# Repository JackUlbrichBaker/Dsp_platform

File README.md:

### Digital Delay Pedal

This is a git repo to track changes in this digital delay pedal

Using the STM32H750 MCU, PCM3060 CODEC and the AS4C16M32MSA Memory ICs

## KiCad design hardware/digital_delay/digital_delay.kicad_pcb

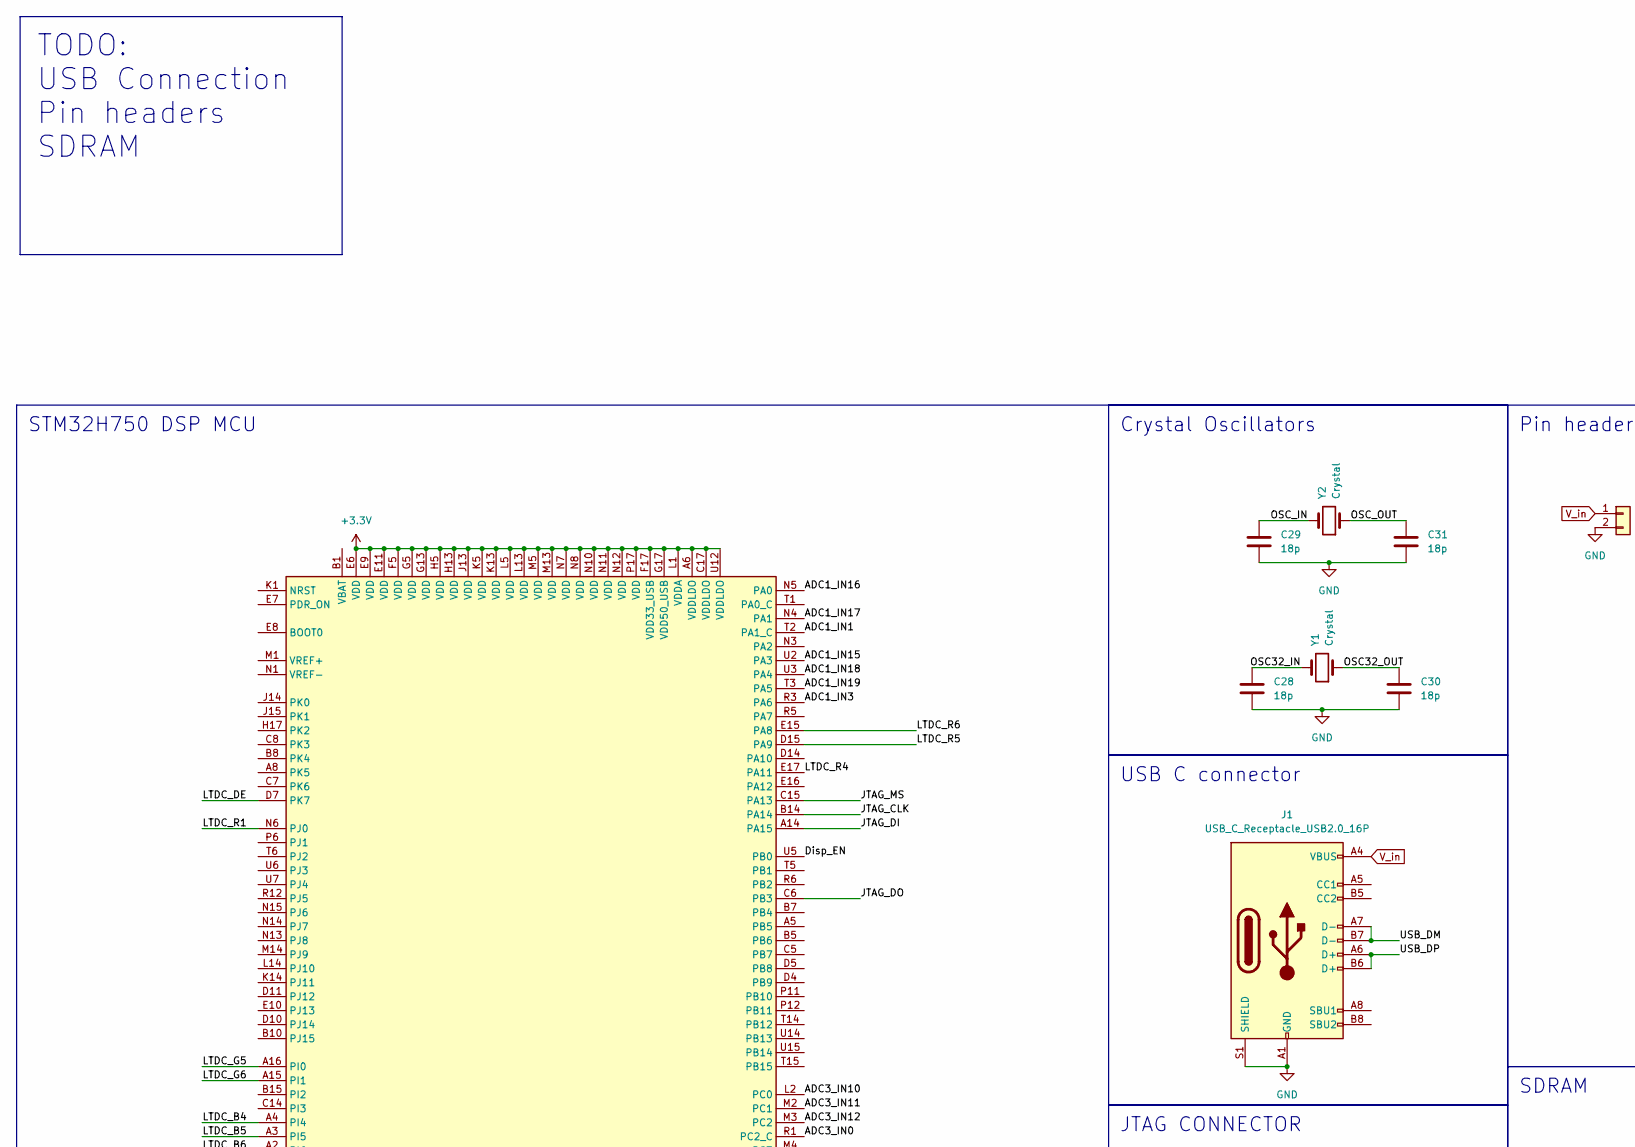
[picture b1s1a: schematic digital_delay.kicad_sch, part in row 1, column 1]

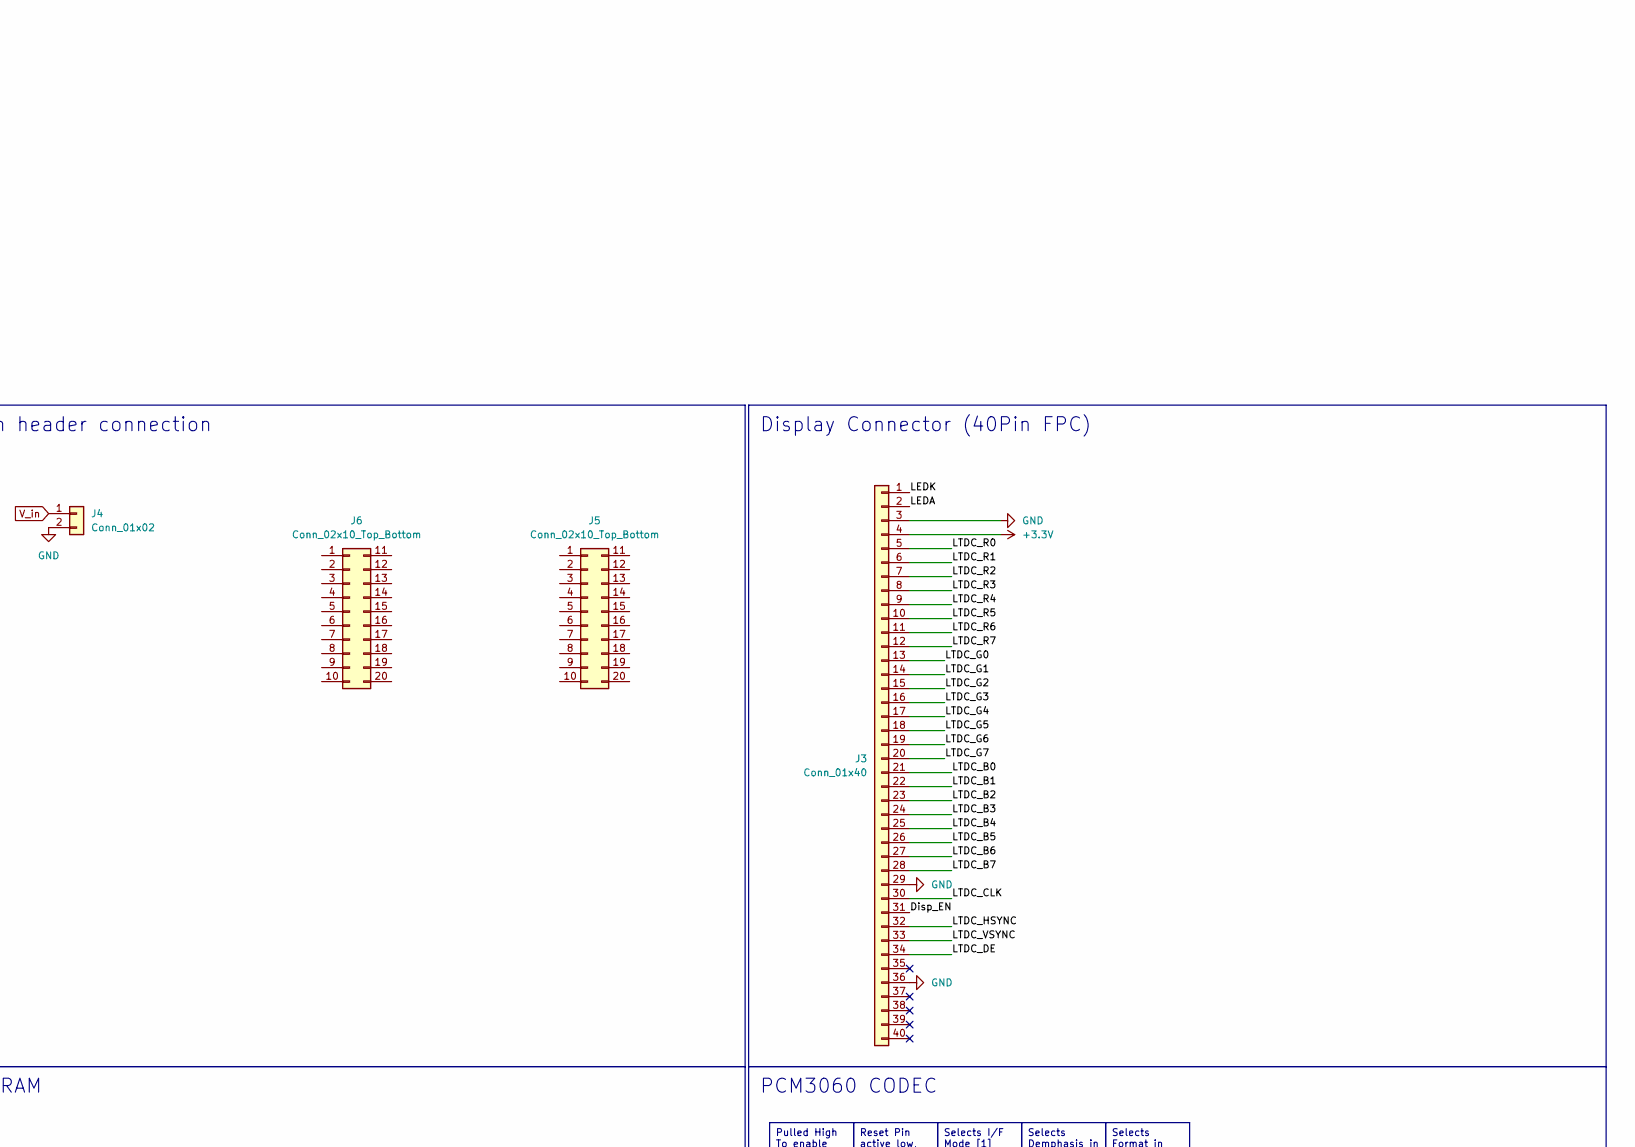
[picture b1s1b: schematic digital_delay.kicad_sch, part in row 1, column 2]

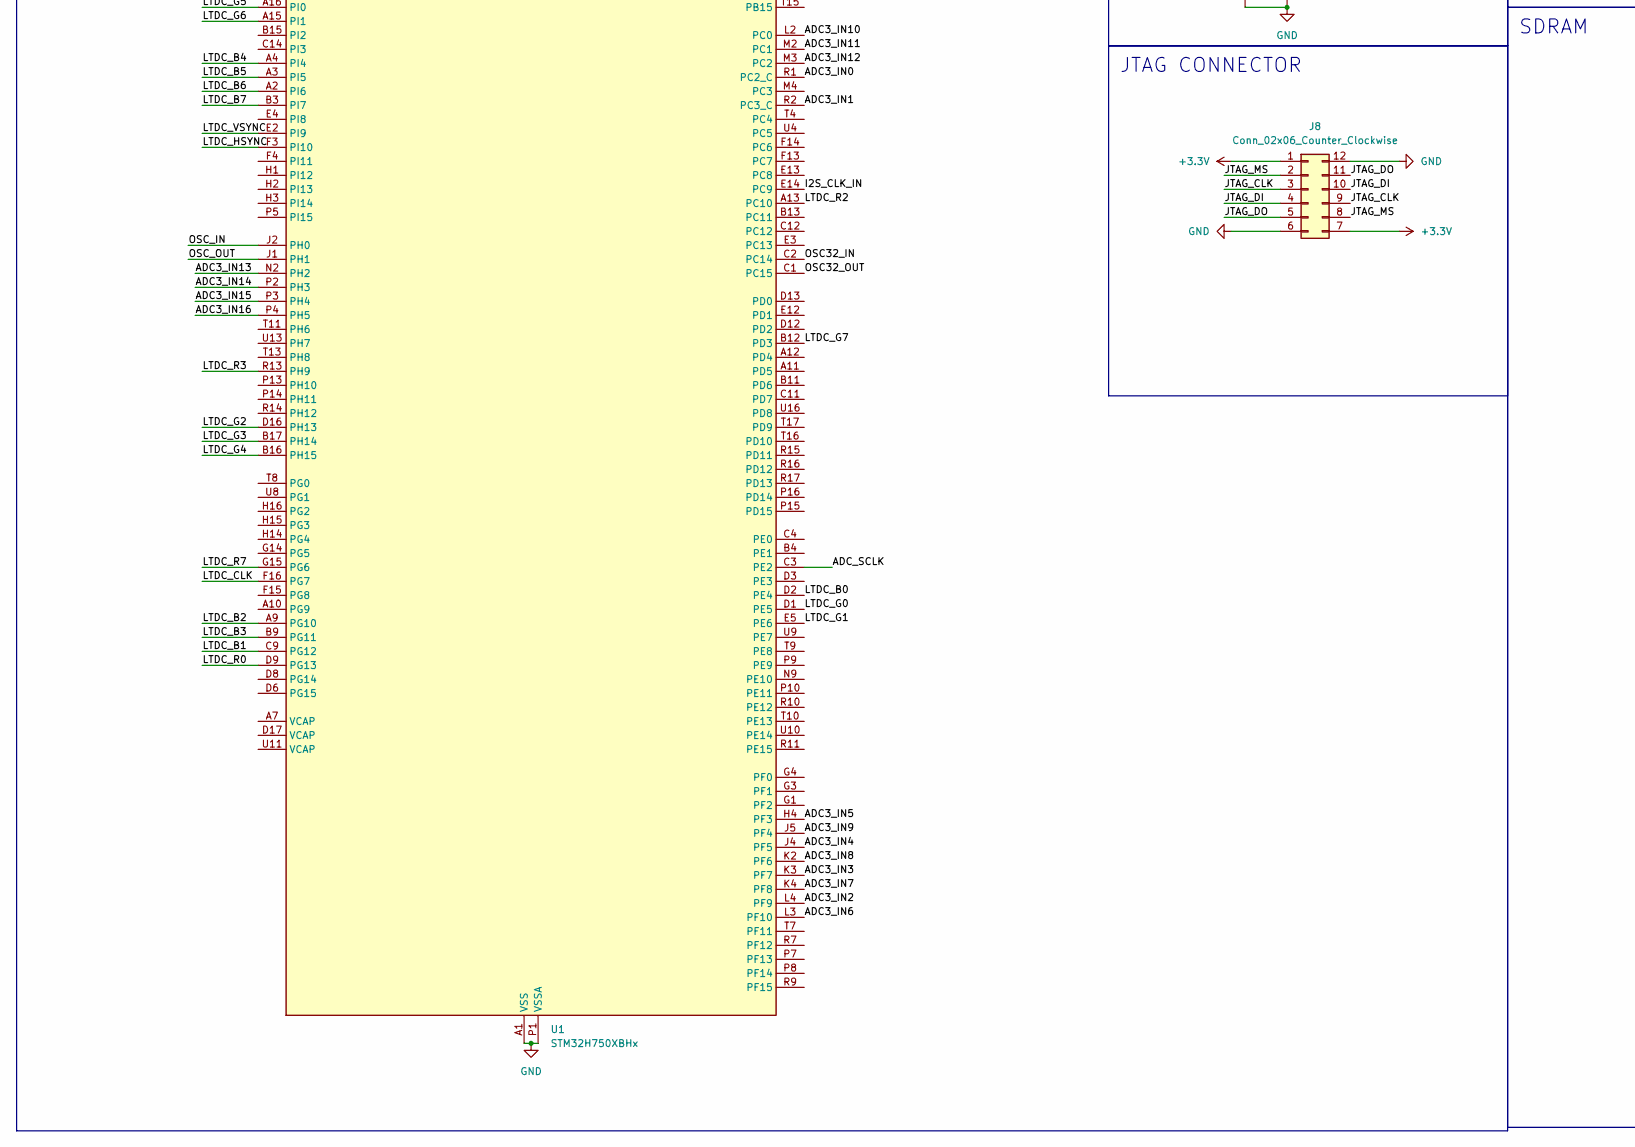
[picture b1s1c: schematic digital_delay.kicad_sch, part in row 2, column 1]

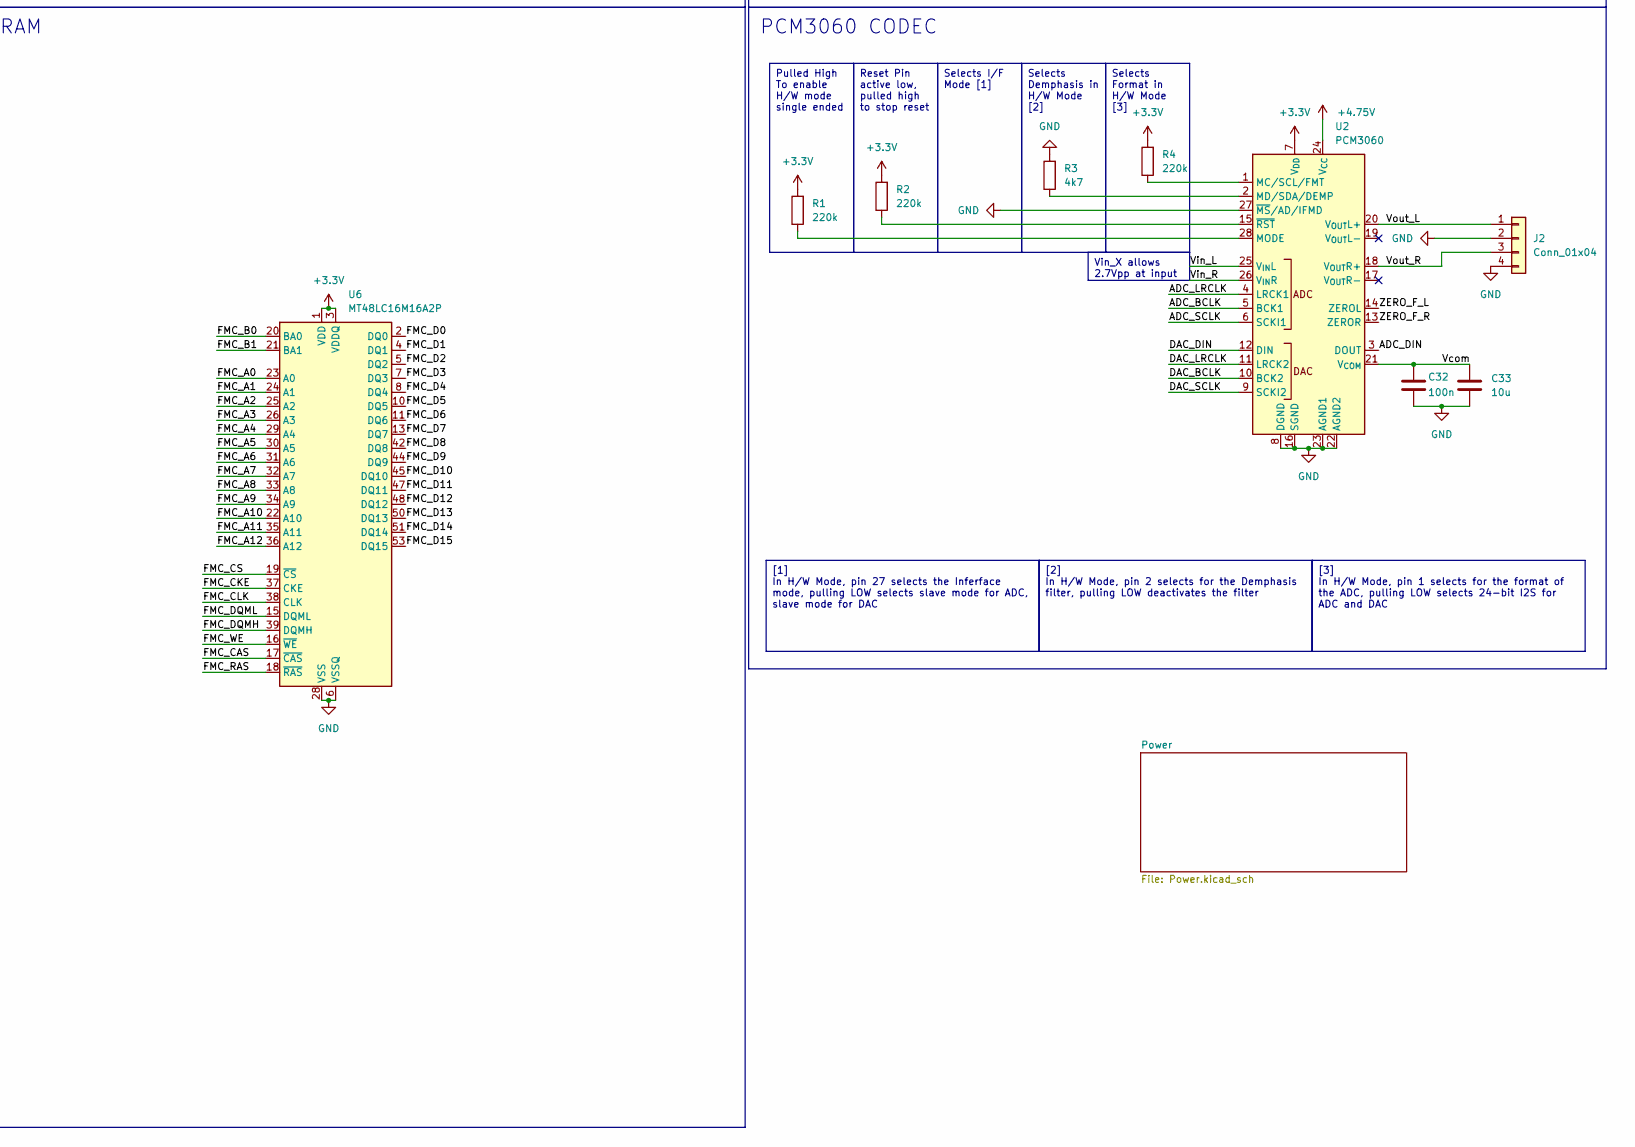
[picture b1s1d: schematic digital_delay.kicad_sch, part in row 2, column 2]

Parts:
C28, C29, C30, C31: 18p; C_0201_0603Metric_Pad0.64x0.40mm_HandSolder
C32: 100n; C_0201_0603Metric_Pad0.64x0.40mm_HandSolder
C33: 10u; C_0201_0603Metric_Pad0.64x0.40mm_HandSolder
J1: USB_C_Receptacle_USB2.0_16P
J2: Conn_01x04; PinHeader_1x04_P2.54mm_Vertical
J3: Conn_01x40; Hirose_FH12-40S-0.5SH_1x40-1MP_P0.50mm_Horizontal
J4: Conn_01x02; PinHeader_1x02_P2.54mm_Vertical
J5, J6: Conn_02x10_Top_Bottom; PinHeader_2x10_P2.54mm_Vertical
J8: Conn_02x06_Counter_Clockwise
R1, R2, R4: 220k; R_0201_0603Metric_Pad0.64x0.40mm_HandSolder
R3: 4k7; R_0201_0603Metric_Pad0.64x0.40mm_HandSolder
U1: STM32H750XBHx; TFBGA-265_14x14mm_Layout17x17_P0.8mm
U2: PCM3060; TSSOP-28_4.4x9.7mm_P0.65mm
U6: MT48LC16M16A2P; TSOP-II-54_22.2x10.16mm_P0.8mm
Y1, Y2: Crystal; Crystal_SMD_0603-2Pin_6.0x3.5mm

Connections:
+3.3V: J3.4, J8.1, J8.7, R1.2, R2.2, R4.2, U1.A6 (VDDLDO), U1.C17 (VDDLDO), U1.E6 (VDD), U1.E9 (VDD), U1.E11 (VDD), U1.F5 (VDD), U1.F17 (VDD33_USB), U1.G5 (VDD), U1.G13 (VDD), U1.G17 (VDD50_USB), U1.H5 (VDD), U1.H13 (VDD), U1.J13 (VDD), U1.K5 (VDD), U1.K13 (VDD), U1.L1 (VDDA), U1.L5 (VDD), U1.L13 (VDD), U1.M5 (VDD), U1.M13 (VDD), U1.N7 (VDD), U1.N8 (VDD), U1.N10 (VDD), U1.N11 (VDD), U1.N12 (VDD), U1.P17 (VDD), U1.U12 (VDDLDO), U2.7 (V_{DD}), U6.1 (VDD), U6.3 (VDDQ), U6.9 (VDDQ), U6.14 (VDD), U6.27 (VDD), U6.43 (VDDQ), U6.49 (VDDQ); also elsewhere on the board
+4.75V: U2.24 (V_{CC}); also elsewhere on the board
/ADC1_IN1: U1.T2 (PA1_C)
/ADC1_IN3: U1.R3 (PA6)
/ADC1_IN15: U1.U2 (PA3)
/ADC1_IN16: U1.N5 (PA0)
/ADC1_IN17: U1.N4 (PA1)
/ADC1_IN18: U1.U3 (PA4)
/ADC1_IN19: U1.T3 (PA5)
/ADC3_IN0: U1.R1 (PC2_C)
/ADC3_IN1: U1.R2 (PC3_C)
/ADC3_IN2: U1.L4 (PF9)
/ADC3_IN3: U1.K3 (PF7)
/ADC3_IN4: U1.J4 (PF5)
/ADC3_IN5: U1.H4 (PF3)
/ADC3_IN6: U1.L3 (PF10)
/ADC3_IN7: U1.K4 (PF8)
/ADC3_IN8: U1.K2 (PF6)
/ADC3_IN9: U1.J5 (PF4)
/ADC3_IN10: U1.L2 (PC0)
/ADC3_IN11: U1.M2 (PC1)
/ADC3_IN12: U1.M3 (PC2)
/ADC3_IN13: U1.N2 (PH2)
/ADC3_IN14: U1.P2 (PH3)
/ADC3_IN15: U1.P3 (PH4)
/ADC3_IN16: U1.P4 (PH5)
/ADC_BCLK: U2.5 (BCK1)
/ADC_DIN: U2.3 (DOUT)
/ADC_LRCLK: U2.4 (LRCK1)
/ADC_SCLK: U1.C3 (PE2), U2.6 (SCKI1)
/DAC_BCLK: U2.10 (BCK2)
/DAC_DIN: U2.12 (DIN)
/DAC_LRCLK: U2.11 (LRCK2)
/DAC_SCLK: U2.9 (SCKI2)
/Disp_EN: J3.31, U1.U5 (PB0)
/FMC_A0: U6.23 (A0)
/FMC_A1: U6.24 (A1)
/FMC_A2: U6.25 (A2)
/FMC_A3: U6.26 (A3)
/FMC_A4: U6.29 (A4)
/FMC_A5: U6.30 (A5)
/FMC_A6: U6.31 (A6)
/FMC_A7: U6.32 (A7)
/FMC_A8: U6.33 (A8)
/FMC_A9: U6.34 (A9)
/FMC_A10: U6.22 (A10)
/FMC_A11: U6.35 (A11)
/FMC_A12: U6.36 (A12)
/FMC_B0: U6.20 (BA0)
/FMC_B1: U6.21 (BA1)
/FMC_CAS: U6.17 (~CAS)
/FMC_CKE: U6.37 (CKE)
/FMC_CLK: U6.38 (CLK)
/FMC_CS: U6.19 (~CS)
/FMC_D0: U6.2 (DQ0)
/FMC_D1: U6.4 (DQ1)
/FMC_D2: U6.5 (DQ2)
/FMC_D3: U6.7 (DQ3)
/FMC_D4: U6.8 (DQ4)
/FMC_D5: U6.10 (DQ5)
/FMC_D6: U6.11 (DQ6)
/FMC_D7: U6.13 (DQ7)
/FMC_D8: U6.42 (DQ8)
/FMC_D9: U6.44 (DQ9)
/FMC_D10: U6.45 (DQ10)
/FMC_D11: U6.47 (DQ11)
/FMC_D12: U6.48 (DQ12)
/FMC_D13: U6.50 (DQ13)
/FMC_D14: U6.51 (DQ14)
/FMC_D15: U6.53 (DQ15)
/FMC_DQMH: U6.39 (DQMH)
/FMC_DQML: U6.15 (DQML)
/FMC_RAS: U6.18 (~RAS)
/FMC_WE: U6.16 (~WE)
/I2S_CLK_IN: U1.E14 (PC9)
/JTAG_CLK: J8.3, J8.9, U1.B14 (PA14)
/JTAG_DI: J8.4, J8.10, U1.A14 (PA15)
/JTAG_DO: J8.5, J8.11, U1.C6 (PB3)
/JTAG_MS: J8.2, J8.8, U1.C15 (PA13)
/LEDA: J3.2
/LEDK: J3.1
/LTDC_B0: J3.21, U1.D2 (PE4)
/LTDC_B1: J3.22, U1.C9 (PG12)
/LTDC_B2: J3.23, U1.A9 (PG10)
/LTDC_B3: J3.24, U1.B9 (PG11)
/LTDC_B4: J3.25, U1.A4 (PI4)
/LTDC_B5: J3.26, U1.A3 (PI5)
/LTDC_B6: J3.27, U1.A2 (PI6)
/LTDC_B7: J3.28, U1.B3 (PI7)
/LTDC_CLK: J3.30, U1.F16 (PG7)
/LTDC_DE: J3.34, U1.D7 (PK7)
/LTDC_G0: J3.13, U1.D1 (PE5)
/LTDC_G1: J3.14, U1.E5 (PE6)
/LTDC_G2: J3.15, U1.D16 (PH13)
/LTDC_G3: J3.16, U1.B17 (PH14)
/LTDC_G4: J3.17, U1.B16 (PH15)
/LTDC_G5: J3.18, U1.A16 (PI0)
/LTDC_G6: J3.19, U1.A15 (PI1)
/LTDC_G7: J3.20, U1.B12 (PD3)
/LTDC_HSYNC: J3.32, U1.F3 (PI10)
/LTDC_R0: J3.5, U1.D9 (PG13)
/LTDC_R1: J3.6, U1.N6 (PJ0)
/LTDC_R2: J3.7, U1.A13 (PC10)
/LTDC_R3: J3.8, U1.R13 (PH9)
/LTDC_R4: J3.9, U1.E17 (PA11)
/LTDC_R5: J3.10, U1.D15 (PA9)
/LTDC_R6: J3.11, U1.E15 (PA8)
/LTDC_R7: J3.12, U1.G15 (PG6)
/LTDC_VSYNC: J3.33, U1.E2 (PI9)
/OSC32_IN: C28.1, U1.C2 (PC14), Y1.2
/OSC32_OUT: C30.1, U1.C1 (PC15), Y1.1
/OSC_IN: C29.1, U1.J2 (PH0), Y2.2
/OSC_OUT: C31.1, U1.J1 (PH1), Y2.1
/Vcom: C32.1, C33.1, U2.21 (V_{COM})
/Vin_L: U2.25 (V_{IN}L)
/Vin_R: U2.26 (V_{IN}R)
/Vout_L: J2.1, U2.20 (V_{OUT}L+)
/Vout_R: J2.3, U2.18 (V_{OUT}R+)
/ZERO_F_L: U2.14 (ZEROL)
/ZERO_F_R: U2.13 (ZEROR)
GND: C28.2, C29.2, C30.2, C31.2, C32.2, C33.2, J1.A1 (GND), J1.A12 (GND), J1.B1 (GND), J1.B12 (GND), J1.S1 (SHIELD), J2.2, J2.4, J3.3, J3.29, J3.36, J4.2, J8.6, J8.12, R3.2, U1.A1 (VSS), U1.A17 (VSS), U1.B2 (VSS), U1.B6 (VSS), U1.C10 (VSS), U1.C13 (VSS), U1.C16 (VSS), U1.F1 (VSS), U1.F2 (VSS), U1.G2 (VSS), U1.G7 (VSS), U1.G8 (VSS), U1.G9 (VSS), U1.G10 (VSS), U1.G11 (VSS), U1.G16 (VSS), U1.H7 (VSS), U1.H8 (VSS), U1.H9 (VSS), U1.H10 (VSS), U1.H11 (VSS), U1.J3 (VSS), U1.J7 (VSS), U1.J8 (VSS), U1.J9 (VSS), U1.J10 (VSS), U1.J11 (VSS), U1.J16 (VSS), U1.J17 (VSS), U1.K7 (VSS), U1.K8 (VSS), U1.K9 (VSS), U1.K10 (VSS), U1.K11 (VSS), U1.K15 (VSS), U1.L7 (VSS), U1.L8 (VSS), U1.L9 (VSS), U1.L10 (VSS), U1.L11 (VSS), U1.L15 (VSS), U1.M15 (VSS), U1.N16 (VSS), U1.P1 (VSSA), U1.R4 (VSS), U1.R8 (VSS), U1.T12 (VSS), U1.U1 (VSS), U1.U17 (VSS), U2.8 (DGND), U2.16 (SGND), U2.22 (AGND2), U2.23 (AGND1), U2.27 (~MS/AD/IFMD), U6.6 (VSSQ), U6.12 (VSSQ), U6.28 (VSS), U6.41 (VSS), U6.46 (VSSQ), U6.52 (VSSQ), U6.54 (VSS); also elsewhere on the board
unnamed: J1.A6 (D+), J1.B6 (D+)
unnamed: J1.A7 (D-), J1.B7 (D-)
unnamed: R4.1, U2.1 (MC/SCL/FMT)
unnamed: R3.1, U2.2 (MD/SDA/DEMP)
unnamed: R1.1, U2.28 (MODE)
unnamed: R2.1, U2.15 (~RST)
V_in: J1.A4 (VBUS), J1.A9 (VBUS), J1.B4 (VBUS), J1.B9 (VBUS), J4.1; also elsewhere on the board

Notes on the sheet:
Crystal Oscillators
PCM3060 CODEC
Reset Pin active low, pulled high to stop reset
Pin header connection
Selects Format in H/W Mode [3]
[3] In H/W Mode, pin 1 selects for the format of the ADC, pulling LOW selects 24-bit I2S for ADC and DAC
Selects I/F Mode [1]
Pulled High To enable H/W mode single ended
[2] In H/W Mode, pin 2 selects for the Demphasis filter, pulling LOW deactivates the filter
[1] In H/W Mode, pin 27 selects the Inferface mode, pulling LOW selects slave mode for ADC, slave mode for DAC
USB C connector
SDRAM
TODO: USB Connection Pin headers SDRAM
Selects Demphasis in H/W Mode [2]
STM32H750 DSP MCU
Display Connector (40Pin FPC)
Vin_X allows 2.7Vpp at input
JTAG CONNECTOR

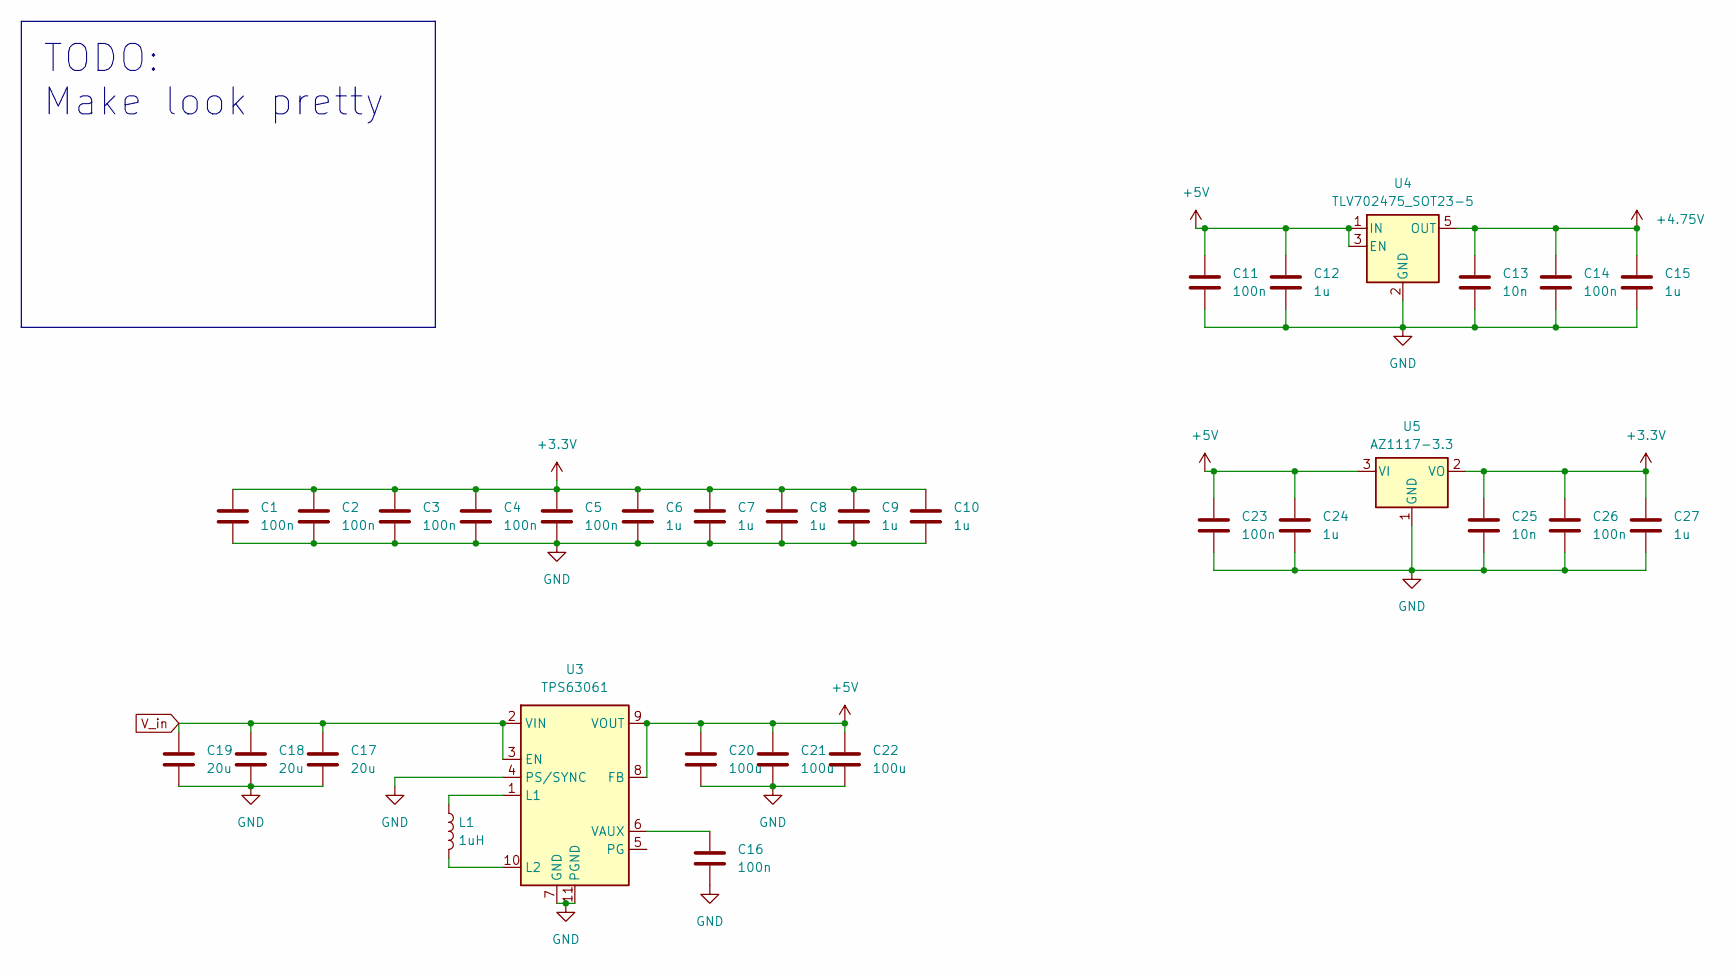
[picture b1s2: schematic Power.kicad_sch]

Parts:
C1, C2, C3, C4, C5, C11, C14, C16, C23, C26: 100n; C_0201_0603Metric_Pad0.64x0.40mm_HandSolder
C6, C7, C8, C9, C10, C12, C15, C24, C27: 1u; C_0201_0603Metric_Pad0.64x0.40mm_HandSolder
C13, C25: 10n; C_0201_0603Metric_Pad0.64x0.40mm_HandSolder
C17, C18, C19: 20u; C_0201_0603Metric_Pad0.64x0.40mm_HandSolder
C20, C21, C22: 100u; C_0201_0603Metric_Pad0.64x0.40mm_HandSolder
L1: 1uH; Crystal_SMD_0603-2Pin_6.0x3.5mm_HandSoldering
U3: TPS63061; Texas_S-PWSON-N10_ThermalVias
U4: TLV702475_SOT23-5; SOT-23-5
U5: AZ1117-3.3; SOT-223-3_TabPin2

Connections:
+3.3V: C1.1, C2.1, C3.1, C4.1, C5.1, C6.1, C7.1, C8.1, C9.1, C10.1, C25.1, C26.1, C27.1, U5.2 (VO); also elsewhere on the board
+4.75V: C13.1, C14.1, C15.1, U4.5 (OUT); also elsewhere on the board
+5V: C11.1, C12.1, C20.1, C21.1, C22.1, C23.1, C24.1, U3.8 (FB), U3.9 (VOUT), U4.1 (IN), U4.3 (EN), U5.3 (VI)
GND: C1.2, C2.2, C3.2, C4.2, C5.2, C6.2, C7.2, C8.2, C9.2, C10.2, C11.2, C12.2, C13.2, C14.2, C15.2, C16.2, C17.2, C18.2, C19.2, C20.2, C21.2, C22.2, C23.2, C24.2, C25.2, C26.2, C27.2, U3.4 (PS/SYNC), U3.7 (GND), U3.11 (PGND), U4.2 (GND), U5.1 (GND); also elsewhere on the board
unnamed: L1.1, U3.1 (L1)
unnamed: L1.2, U3.10 (L2)
unnamed: C16.1, U3.6 (VAUX)
V_in: C17.1, C18.1, C19.1, U3.2 (VIN), U3.3 (EN); also elsewhere on the board

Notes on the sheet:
TODO: Make look pretty

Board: 2 copper layers, 51 parts (0 on the bottom side), 49 nets, no tracks yet.

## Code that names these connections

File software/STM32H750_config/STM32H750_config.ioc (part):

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Mcu.Name=STM32H750XBHx
Mcu.Package=TFBGA240
Mcu.UserName=STM32H750XBHx
PA10.Mode=OTG/Dual_Role_Device
PA10.Signal=USB_OTG_FS_ID
PA11.Mode=OTG/Dual_Role_Device
PA11.Signal=USB_OTG_FS_DM
PA12.Mode=OTG/Dual_Role_Device
PA12.Signal=USB_OTG_FS_DP
PA13\ (JTMS/SWDIO).Mode=JTAG_4_pins
PA13\ (JTMS/SWDIO).Signal=DEBUG_JTMS-SWDIO
PA14\ (JTCK/SWCLK).Mode=JTAG_4_pins
PA14\ (JTCK/SWCLK).Signal=DEBUG_JTCK-SWCLK
PA15\ (JTDI).Mode=JTAG_4_pins
PA15\ (JTDI).Signal=DEBUG_JTDI
PA2.Mode=RGB888
PA2.Signal=LTDC_R1
PA5.Mode=RGB888
PA5.Signal=LTDC_R4
PA8.Mode=RGB888
PA8.Signal=LTDC_R6
PA9.Mode=Activate_VBUS
PA9.Signal=USB_OTG_FS_VBUS
PB3\ (JTDO/TRACESWO).Mode=JTAG_4_pins
PB3\ (JTDO/TRACESWO).Signal=DEBUG_JTDO-SWO
PB5.Mode=SdramChipSelect2_1
PB5.Signal=FMC_SDCKE1
PB6.Mode=SdramChipSelect2_1
PB6.Signal=FMC_SDNE1
PC0.Mode=RGB888
PC0.Signal=LTDC_R5
PC10.Mode=RGB888
PC10.Signal=LTDC_R2
PC14-OSC32_IN\ (OSC32_IN).Mode=LSE-External-Oscillator
PC14-OSC32_IN\ (OSC32_IN).Signal=RCC_OSC32_IN
PC15-OSC32_OUT\ (OSC32_OUT).Mode=LSE-External-Oscillator
PC15-OSC32_OUT\ (OSC32_OUT).Signal=RCC_OSC32_OUT
PC6.Mode=RGB888
PC6.Signal=LTDC_HSYNC
PD0.Signal=FMC_D2_DA2
PD1.Signal=FMC_D3_DA3
PD10.Signal=FMC_D15_DA15
PD14.Signal=FMC_D0_DA0
PD15.Signal=FMC_D1_DA1
PD3.Mode=RGB888
PD3.Signal=LTDC_G7
PD6.Mode=SAI_A_MasterWithClock
PD6.Signal=SAI1_SD_A
PD8.Signal=FMC_D13_DA13
PD9.Signal=FMC_D14_DA14
PE10.Signal=FMC_D7_DA7
PE11.Signal=FMC_D8_DA8
PE12.Signal=FMC_D9_DA9
PE13.Signal=FMC_D10_DA10
PE14.Signal=FMC_D11_DA11
PE15.Signal=FMC_D12_DA12
PE2.Mode=SAI_A_MasterWithClock
PE2.Signal=SAI1_MCLK_A
PE3.Mode=SAI_B_SyncSlave
PE3.Signal=SAI1_SD_B
PE4.Mode=SAI_A_MasterWithClock
PE4.Signal=SAI1_FS_A
PE5.Mode=SAI_A_MasterWithClock
PE5.Signal=SAI1_SCK_A
PE6.Mode=RGB888
PE6.Signal=LTDC_G1
PE7.Signal=FMC_D4_DA4
PE8.Signal=FMC_D5_DA5
PE9.Signal=FMC_D6_DA6
PF0.Signal=FMC_A0
PF1.Signal=FMC_A1
PF11.Signal=FMC_SDNRAS
PF12.Signal=FMC_A6
PF13.Signal=FMC_A7
PF14.Signal=FMC_A8
PF15.Signal=FMC_A9
PF2.Signal=FMC_A2
PF3.Signal=FMC_A3
PF4.Signal=FMC_A4
PF5.Signal=FMC_A5
PG0.Signal=FMC_A10
PG1.Signal=FMC_A11
PG10.Mode=RGB888
PG10.Signal=LTDC_G3
PG11.Mode=RGB888
PG11.Signal=LTDC_B3
PG13.Mode=RGB888
PG13.Signal=LTDC_R0
PG14.Mode=RGB888
PG14.Signal=LTDC_B0
PG15.Signal=FMC_SDNCAS
PG2.Signal=FMC_A12
PG4.Signal=FMC_A14_BA0
PG5.Signal=FMC_A15_BA1
PG6.Mode=RGB888
PG6.Signal=LTDC_R7
PG7.Mode=RGB888
PG7.Signal=LTDC_CLK
PG8.Signal=FMC_SDCLK
PH0-OSC_IN\ (PH0).Mode=HSE-External-Oscillator
PH0-OSC_IN\ (PH0).Signal=RCC_OSC_IN
PH1-OSC_OUT\ (PH1).Mode=HSE-External-Oscillator
PH1-OSC_OUT\ (PH1).Signal=RCC_OSC_OUT
PH10.Signal=FMC_D18
PH11.Signal=FMC_D19
PH12.Signal=FMC_D20
PH13.Signal=FMC_D21
PH14.Signal=FMC_D22
PH15.Signal=FMC_D23
PH5.Signal=FMC_SDNWE
PH8.Signal=FMC_D16
PH9.Signal=FMC_D17
PI0.Signal=FMC_D24
PI1.Signal=FMC_D25
PI10.Signal=FMC_D31
PI11.Mode=RGB888
PI11.Signal=LTDC_G6
PI13.Mode=RGB888
PI13.Signal=LTDC_VSYNC
PI2.Signal=FMC_D26
PI3.Signal=FMC_D27
PI4.Mode=RGB888
PI4.Signal=LTDC_B4
PI5.Mode=RGB888
PI5.Signal=LTDC_B5
PI6.Signal=FMC_D28
PI7.Signal=FMC_D29
PI9.Signal=FMC_D30
PJ11.Mode=RGB888
PJ11.Signal=LTDC_G4
PJ13.Mode=RGB888
PJ13.Signal=LTDC_B1
PJ14.Mode=RGB888
PJ14.Signal=LTDC_B2
PJ2.Mode=RGB888
PJ2.Signal=LTDC_R3
PJ7.Mode=RGB888
PJ7.Signal=LTDC_G0
PJ9.Mode=RGB888
PJ9.Signal=LTDC_G2
PK0.Mode=RGB888
PK0.Signal=LTDC_G5
PK5.Mode=RGB888
PK5.Signal=LTDC_B6
PK6.Mode=RGB888
PK6.Signal=LTDC_B7
PK7.Mode=RGB888
PK7.Signal=LTDC_DE
RCC.SYSCLKFreq_VALUE=64000000
board=custom

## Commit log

2024-04-16 inital commit :)
2024-04-22 howdy incomplete schematic
2024-04-24 rough design 0.1
2024-04-24 bare minimum readme
2024-04-24 add comments
2024-04-26 memory
2024-04-27 basic design rules for 8 layer PCB
